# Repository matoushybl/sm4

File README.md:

# SM4 Stepper motor controller

This repository contains everything related to the SM4 Stepper motor controller project.

The project structure is as follows:
```
.github/ ... workflows for CI, releases, etc.
Hardware/ ... everything related to hardware - KiCAD projects, DS, etc.
Poster/ ... source file for a future poster
Software/ ... the controller and embedded firmware
Thesis/ ... the TeX source code for my Master's Thesis
```

## Authors
* Matous Hybl

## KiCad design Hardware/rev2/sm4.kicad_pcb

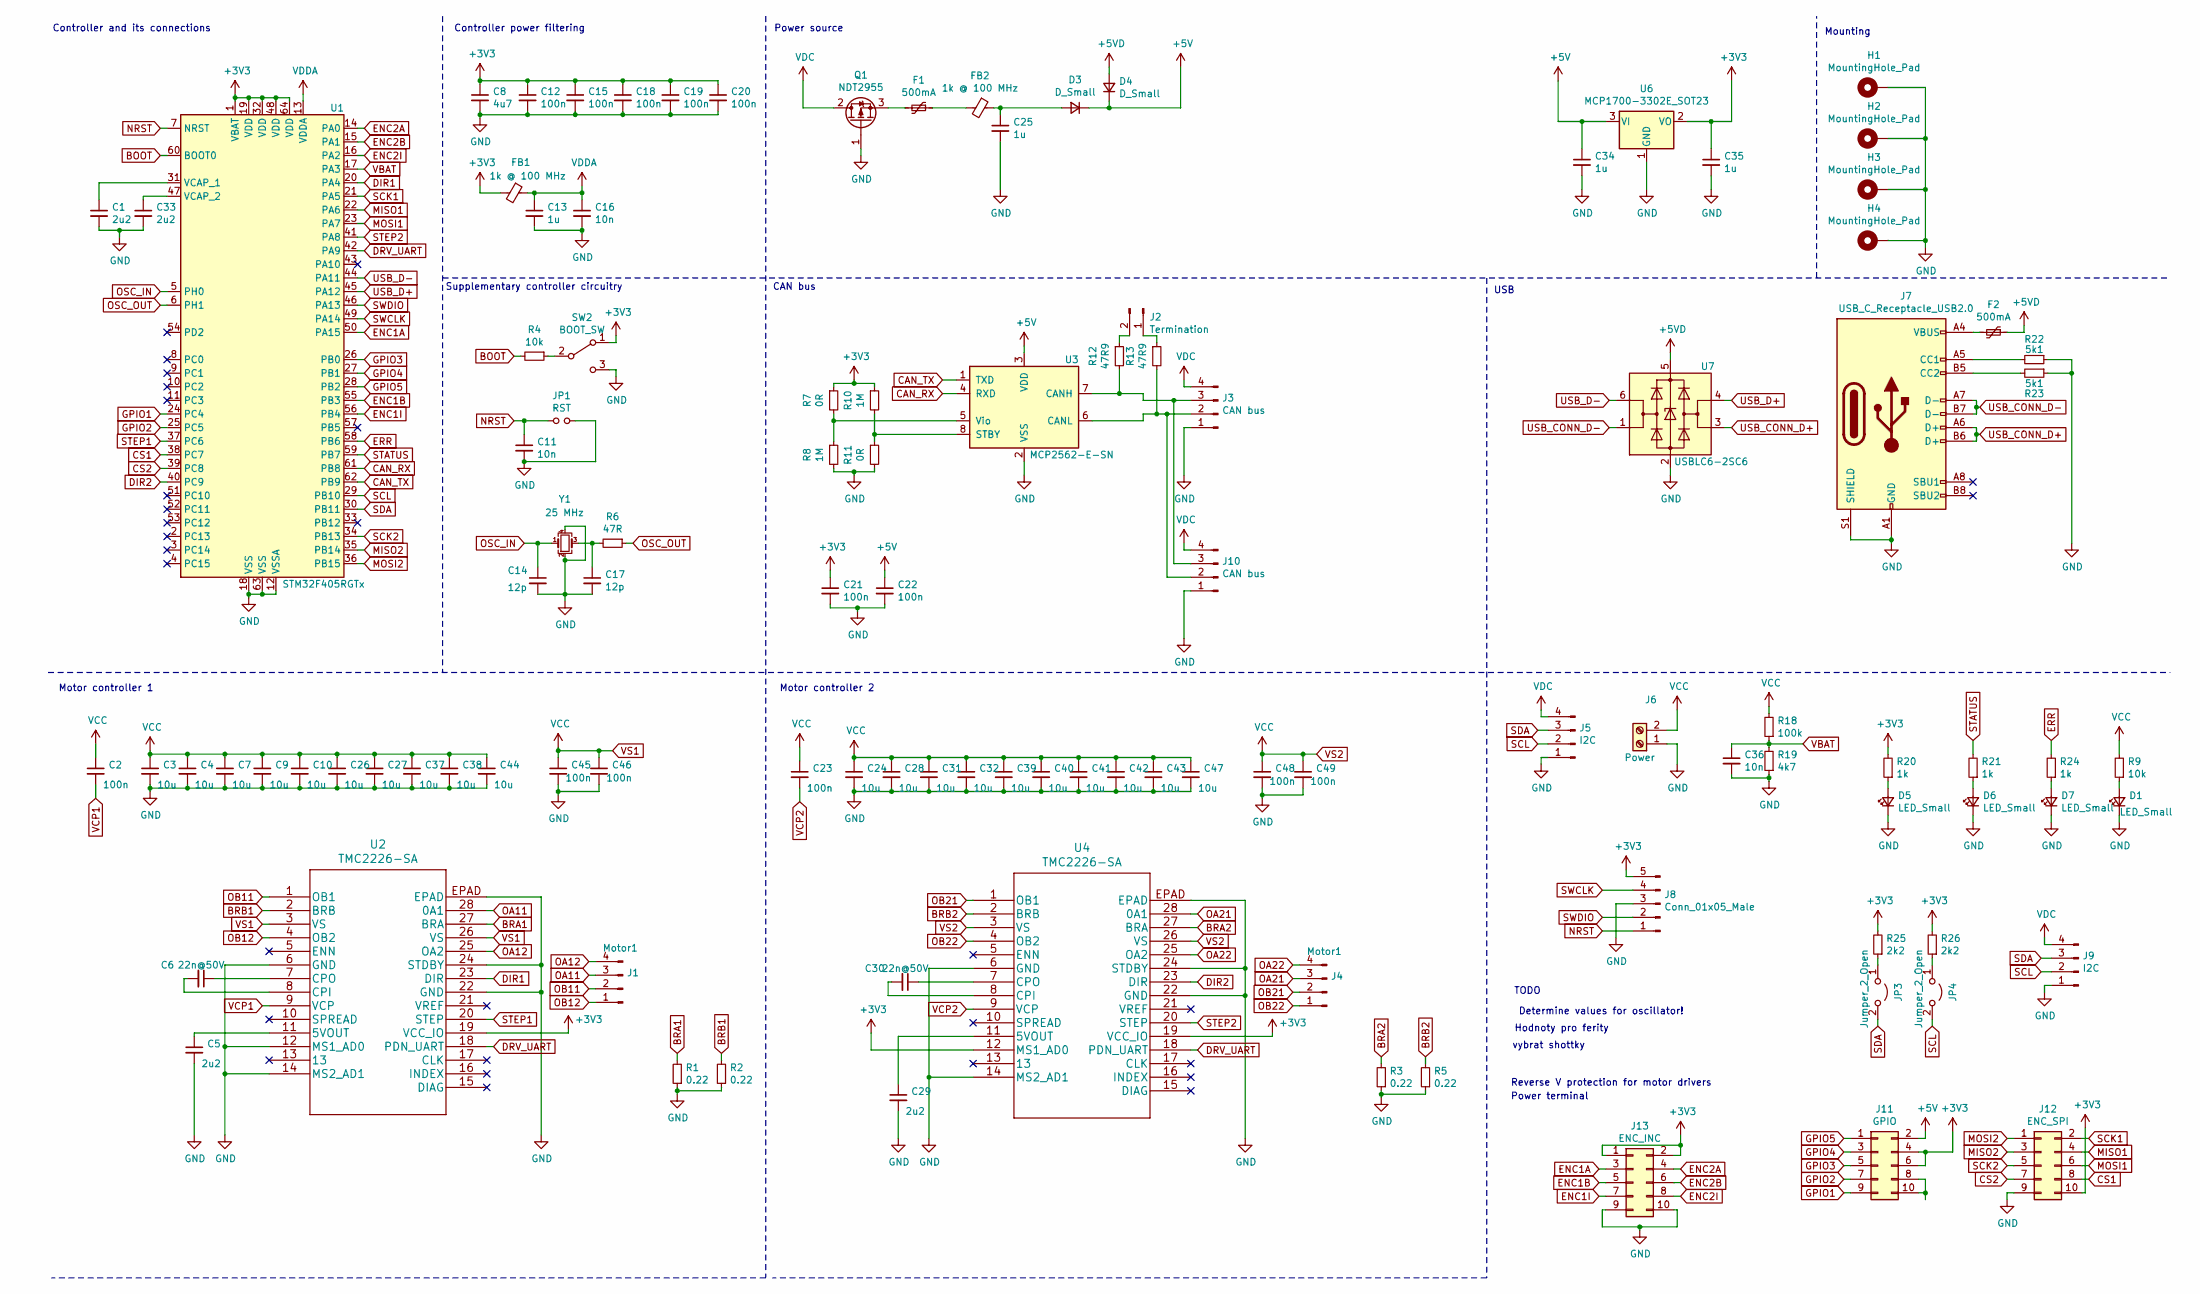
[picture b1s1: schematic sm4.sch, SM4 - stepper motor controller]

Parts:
C1, C33: 2u2; C_0603_1608Metric_Pad1.08x0.95mm_HandSolder; LCSC C23630
C2, C23, C45, C46, C48, C49: 100n; C_0603_1608Metric_Pad1.08x0.95mm_HandSolder; LCSC C14663
C3, C4, C7, C9, C10, C24, C26, C27, C28, C31, C32, C37, C38, C39, C40, C41, C42, C43, C44, C47: 10u; C_1206_3216Metric_Pad1.33x1.80mm_HandSolder; LCSC C13585
C5, C29: 2u2; C_0603_1608Metric_Pad1.08x0.95mm_HandSolder; LCSC C13585
C6, C30: 22n@50V; C_0402_1005Metric_Pad0.74x0.62mm_HandSolder; LCSC C1532
C8: 4u7; C_0603_1608Metric_Pad1.08x0.95mm_HandSolder; LCSC C19666
C11: 10n; C_0603_1608Metric_Pad1.08x0.95mm_HandSolder; LCSC C57112
C12, C15, C18, C19, C20, C21, C22: 100n; C_0402_1005Metric_Pad0.74x0.62mm_HandSolder; LCSC C1525
C13, C34, C35: 1u; C_0603_1608Metric_Pad1.08x0.95mm_HandSolder; LCSC C15849
C14, C17: 12p; C_0402_1005Metric_Pad0.74x0.62mm_HandSolder; LCSC C1547
C16, C36: 10n; C_0402_1005Metric_Pad0.74x0.62mm_HandSolder; LCSC C15195
C25: 1u; C_1206_3216Metric_Pad1.33x1.80mm_HandSolder; LCSC C1848
D1, D5: LED_Small; LED_0603_1608Metric_Pad1.05x0.95mm_HandSolder; LCSC C72038
D3, D4: D_Small; D_SOD-123; LCSC C8598
D6: LED_Small; LED_0603_1608Metric_Pad1.05x0.95mm_HandSolder; LCSC C72043
D7: LED_Small; LED_0603_1608Metric_Pad1.05x0.95mm_HandSolder; LCSC C2286
F1, F2: 500mA; Fuse_1206_3216Metric_Pad1.42x1.75mm_HandSolder; LCSC C70076
FB1, FB2: 1k @ 100 MHz; R_0603_1608Metric_Pad0.98x0.95mm_HandSolder
H1, H2, H3, H4: MountingHole_Pad; MountingHole_3.2mm_M3_Pad
J1, J4: Motor1; PinHeader_1x04_P2.54mm_Horizontal
J2: Termination; PinHeader_1x02_P2.54mm_Vertical
J3: CAN bus; Molex_SPOX_5268-04A_1x04_P2.50mm_Horizontal
J5: I2C; Molex_SPOX_5268-04A_1x04_P2.50mm_Horizontal
J6: Power; TerminalBlock_bornier-2_P5.08mm
J7: USB_C_Receptacle_USB2.0; USB_C_Receptacle_XKB_U262-16XN-4BVC11
J8: Conn_01x05_Male; Molex_SPOX_5267-05A_1x05_P2.50mm_Vertical
J9: I2C; Molex_SPOX_5267-04A_1x04_P2.50mm_Vertical
J10: CAN bus; Molex_SPOX_5267-04A_1x04_P2.50mm_Vertical
J11: GPIO; PinHeader_2x05_P1.27mm_Vertical
J12: ENC_SPI; PinHeader_2x05_P1.27mm_Vertical
J13: ENC_INC; PinHeader_2x05_P1.27mm_Vertical
JP1: RST; SolderJumper-2_P1.3mm_Open_RoundedPad1.0x1.5mm
JP3, JP4: Jumper_2_Open; SolderJumper-2_P1.3mm_Open_TrianglePad1.0x1.5mm
Q1: NDT2955; SOT-223-3_TabPin2; LCSC C194179
R1, R2, R3, R5: 0.22; R_1206_3216Metric_Pad1.30x1.75mm_HandSolder
R4: 10k; R_0402_1005Metric_Pad0.72x0.64mm_HandSolder; LCSC C25744
R6: 47R; R_0402_1005Metric_Pad0.72x0.64mm_HandSolder; LCSC C23182
R7, R11: 0R; R_0402_1005Metric_Pad0.72x0.64mm_HandSolder; LCSC C17168
R8, R10: 1M; R_0402_1005Metric_Pad0.72x0.64mm_HandSolder
R9: 10k; R_0402_1005Metric_Pad0.72x0.64mm_HandSolder; LCSC C25879
R12, R13: 47R9; R_0603_1608Metric_Pad0.98x0.95mm_HandSolder; LCSC C23182
R18: 100k; R_0402_1005Metric_Pad0.72x0.64mm_HandSolder; LCSC C25741
R19: 4k7; R_0402_1005Metric_Pad0.72x0.64mm_HandSolder; LCSC C25900
R20, R21, R24: 1k; R_0402_1005Metric_Pad0.72x0.64mm_HandSolder; LCSC C25879
R22, R23: 5k1; R_0402_1005Metric_Pad0.72x0.64mm_HandSolder; LCSC C25905
R25, R26: 2k2; R_0402_1005Metric_Pad0.72x0.64mm_HandSolder; LCSC C25879
SW2: BOOT_SW; SW_SPDT_PCM12
U1: STM32F405RGTx; LQFP-64_10x10mm_P0.5mm; LCSC C15742
U2, U4: TMC2226-SA
U3: MCP2562-E-SN; SOIC-8_3.9x4.9mm_P1.27mm; LCSC C53609
U6: MCP1700-3302E_SOT23; SOT-23; LCSC C39051
U7: USBLC6-2SC6; SOT-23-6; LCSC C7519
Y1: 25 MHz; Crystal_SMD_3225-4Pin_3.2x2.5mm_HandSoldering; LCSC C9006

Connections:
+3V3: C8.1, C12.1, C15.1, C18.1, C19.1, C20.1, C21.1, C35.1, FB1.2, J8.5, J11.4, J11.6, J12.10, J13.1, J13.2, R7.1, R10.1, R20.2, R25.2, R26.2, SW2.1 (A), U1.1 (VBAT), U1.19 (VDD), U1.32 (VDD), U1.48 (VDD), U1.64 (VDD), U2.19 (VCC_IO), U4.12 (MS1_AD0), U4.19 (VCC_IO), U6.2 (VO)
+5V: C22.1, C34.1, D3.1 (K), D4.1 (K), J11.2, U3.3 (VDD), U6.3 (VI)
+5VD: D4.2 (A), F2.1, U7.5 (VBUS)
BOOT: R4.2, U1.60 (BOOT0)
BRA1: R1.2, U2.27 (BRA)
BRA2: R3.2, U4.27 (BRA)
BRB1: R2.2, U2.2 (BRB)
BRB2: R5.2, U4.2 (BRB)
CAN_RX: U1.61 (PB8), U3.4 (RXD)
CAN_TX: U1.62 (PB9), U3.1 (TXD)
CS1: J12.8, U1.38 (PC7)
CS2: J12.7, U1.39 (PC8)
DIR1: U1.20 (PA4), U2.23 (DIR)
DIR2: U1.40 (PC9), U4.23 (DIR)
DRV_UART: U1.42 (PA9), U2.18 (PDN_UART), U4.18 (PDN_UART)
ENC1A: J13.3, U1.50 (PA15)
ENC1B: J13.5, U1.55 (PB3)
ENC1I: J13.7, U1.56 (PB4)
ENC2A: J13.4, U1.14 (PA0)
ENC2B: J13.6, U1.15 (PA1)
ENC2I: J13.8, U1.16 (PA2)
ERR: R24.2, U1.58 (PB6)
GND: C1.2, C3.2, C4.2, C5.2, C7.2, C8.2, C9.2, C10.2, C11.2, C12.2, C13.2, C14.2, C15.2, C16.2, C17.2, C18.2, C19.2, C20.2, C21.2, C22.2, C24.2, C25.2, C26.2, C27.2, C28.2, C29.2, C31.2, C32.2, C33.2, C34.2, C35.2, C36.2, C37.2, C38.2, C39.2, C40.2, C41.2, C42.2, C43.2, C44.2, C45.2, C46.2, C47.2, C48.2, C49.2, D1.1 (K), D5.1 (K), D6.1 (K), D7.1 (K), H1.1, H2.1, H3.1, H4.1, J3.1, J5.1, J6.1, J7.A1 (GND), J7.A12 (GND), J7.B1 (GND), J7.B12 (GND), J7.S1 (SHIELD), J8.3, J9.1, J10.1, J12.9, J13.9, J13.10, JP1.2, Q1.1 (G), R1.1, R2.1, R3.1, R5.1, R8.2, R11.2, R19.1, R22.1, R23.1, SW2.3 (C), U1.12 (VSSA), U1.18 (VSS), U1.63 (VSS), U2.6 (GND), U2.12 (MS1_AD0), U2.14 (MS2_AD1), U2.22 (GND), U2.24 (STDBY), U2.EPAD, U3.2 (VSS), U4.6 (GND), U4.14 (MS2_AD1), U4.22 (GND), U4.24 (STDBY), U4.EPAD, U6.1 (GND)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
GPIO1: J11.9, U1.24 (PC4)
GPIO2: J11.7, U1.25 (PC5)
GPIO3: J11.5, U1.26 (PB0)
GPIO4: J11.3, U1.27 (PB1)
GPIO5: J11.1, U1.28 (PB2)
MISO1: J12.4, U1.22 (PA6)
MISO2: J12.3, U1.35 (PB14)
MOSI1: J12.6, U1.23 (PA7)
MOSI2: J12.1, U1.36 (PB15)
NRST: C11.1, J8.1, JP1.1, U1.7 (NRST)
unnamed: C1.1, U1.31 (VCAP_1)
unnamed: C5.1, U2.11 (5VOUT)
unnamed: C6.1, U2.7 (CPO)
unnamed: C6.2, U2.8 (CPI)
unnamed: C17.1, R6.2, Y1.3
unnamed: C25.1, D3.2 (A), FB2.1
unnamed: C29.1, U4.11 (5VOUT)
unnamed: C30.1, U4.7 (CPO)
unnamed: C30.2, U4.8 (CPI)
unnamed: C33.1, U1.47 (VCAP_2)
unnamed: D1.2 (A), R9.1
unnamed: D5.2 (A), R20.1
unnamed: D6.2 (A), R21.1
unnamed: D7.2 (A), R24.1
unnamed: F1.1, FB2.2
unnamed: F1.2, Q1.3 (S)
unnamed: F2.2, J7.A4 (VBUS), J7.A9 (VBUS), J7.B4 (VBUS), J7.B9 (VBUS)
unnamed: J2.1, R13.1
unnamed: J2.2, R12.1
unnamed: J7.A5 (CC1), R22.2
unnamed: J7.B5 (CC2), R23.2
unnamed: J3.2, J10.2, R13.2, U3.6 (CANL)
unnamed: J3.3, J10.3, R12.2, U3.7 (CANH)
unnamed: J11.8, J11.10
unnamed: JP3.1 (A), R25.1
unnamed: JP4.1 (A), R26.1
unnamed: R4.1, SW2.2 (B)
unnamed: R7.2, R8.1, U3.5 (Vio)
unnamed: R10.2, R11.1, U3.8 (STBY)
OA11: J1.3, U2.28 (0A1)
OA12: J1.4, U2.25 (OA2)
OA21: J4.3, U4.28 (0A1)
OA22: J4.4, U4.25 (OA2)
OB11: J1.2, U2.1 (OB1)
OB12: J1.1, U2.4 (OB2)
OB21: J4.2, U4.1 (OB1)
OB22: J4.1, U4.4 (OB2)
OSC_IN: C14.1, U1.5 (PH0), Y1.1
OSC_OUT: R6.1, U1.6 (PH1)
SCK1: J12.2, U1.21 (PA5)
SCK2: J12.5, U1.34 (PB13)
SCL: J5.2, J9.2, JP4.2 (B), U1.29 (PB10)
SDA: J5.3, J9.3, JP3.2 (B), U1.30 (PB11)
STATUS: R21.2, U1.59 (PB7)
STEP1: U1.37 (PC6), U2.20 (STEP)
STEP2: U1.41 (PA8), U4.20 (STEP)
SWCLK: J8.4, U1.49 (PA14)
SWDIO: J8.2, U1.46 (PA13)
USB_CONN_D+: J7.A6 (D+), J7.B6 (D+), U7.3 (I/O2)
USB_CONN_D-: J7.A7 (D-), J7.B7 (D-), U7.1 (I/O1)
USB_D+: U1.45 (PA12), U7.4 (I/O2)
USB_D-: U1.44 (PA11), U7.6 (I/O1)
VBAT: C36.1, R18.1, R19.2, U1.17 (PA3)
VCP1: C2.2, U2.9 (VCP)
VCP2: C23.2, U4.9 (VCP)
VDC: J3.4, J5.4, J9.4, J10.4, Q1.2 (D)
VDDA: C13.1, C16.1, FB1.1, U1.13 (VDDA)
VS1: C2.1, C3.1, C4.1, C7.1, C9.1, C10.1, C23.1, C24.1, C26.1, C27.1, C28.1, C31.1, C32.1, C37.1, C38.1, C39.1, C40.1, C41.1, C42.1, C43.1, C44.1, C45.1, C46.1, C47.1, C48.1, C49.1, J6.2, R9.2, R18.2, U2.3 (VS), U2.26 (VS), U4.3 (VS), U4.26 (VS)

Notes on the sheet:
Determine values for oscillator!
Controller and its connections
Controller power filtering
Supplementary controller circuitry
Power source
Mounting
TODO
Hodnoty pro ferity
vybrat shottky
Motor controller 1
Motor controller 2
Reverse V protection for motor drivers
CAN bus
USB
Power terminal

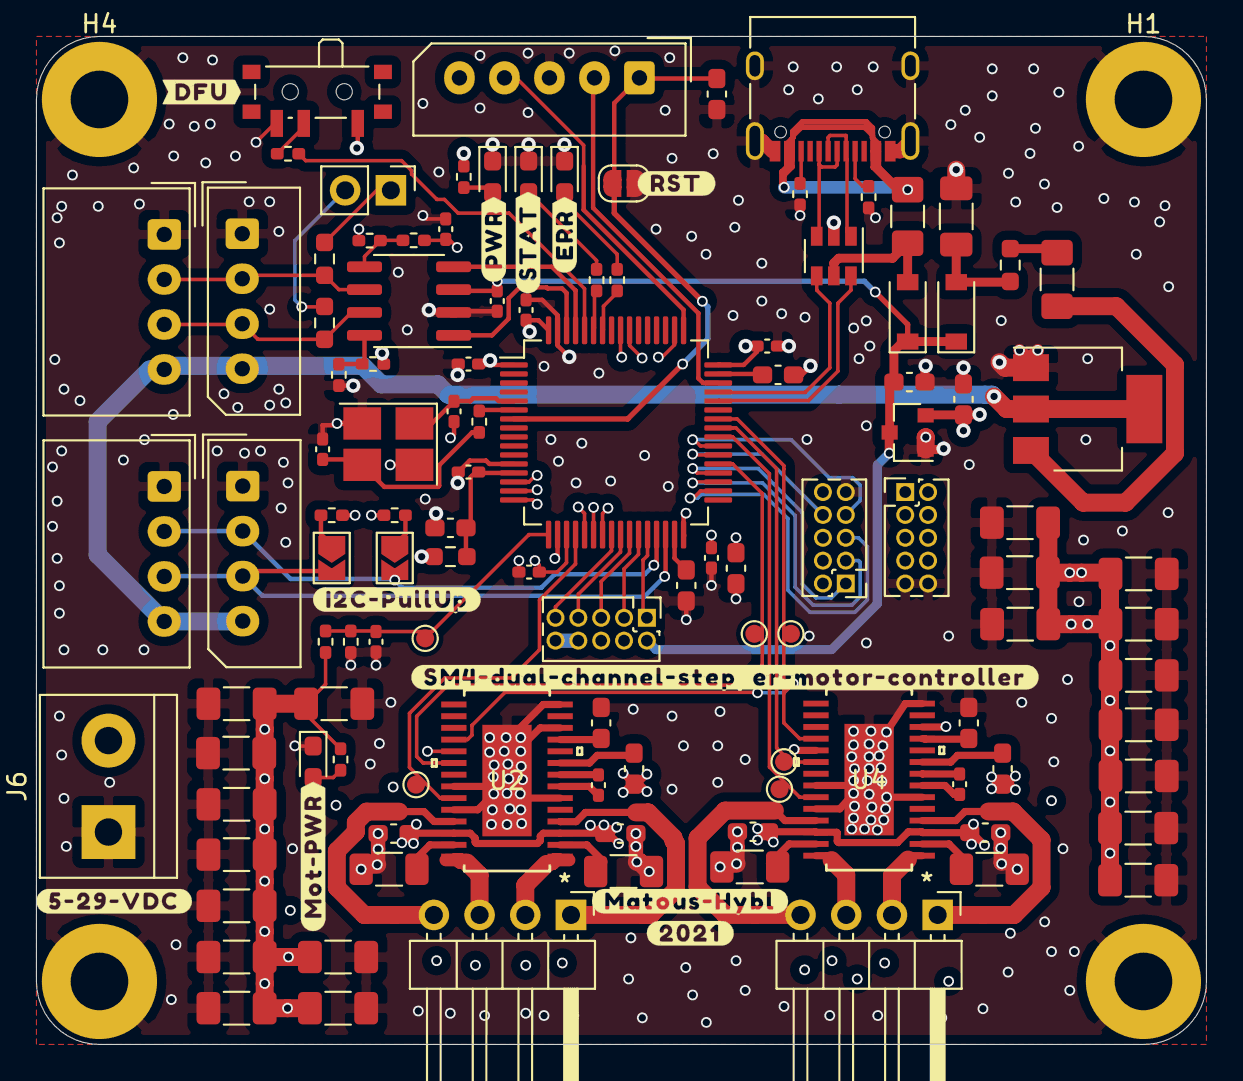
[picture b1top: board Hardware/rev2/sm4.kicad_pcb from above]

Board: 4 copper layers, 65.0 x 56.0 mm, 110 parts (0 on the bottom side), 91 nets.

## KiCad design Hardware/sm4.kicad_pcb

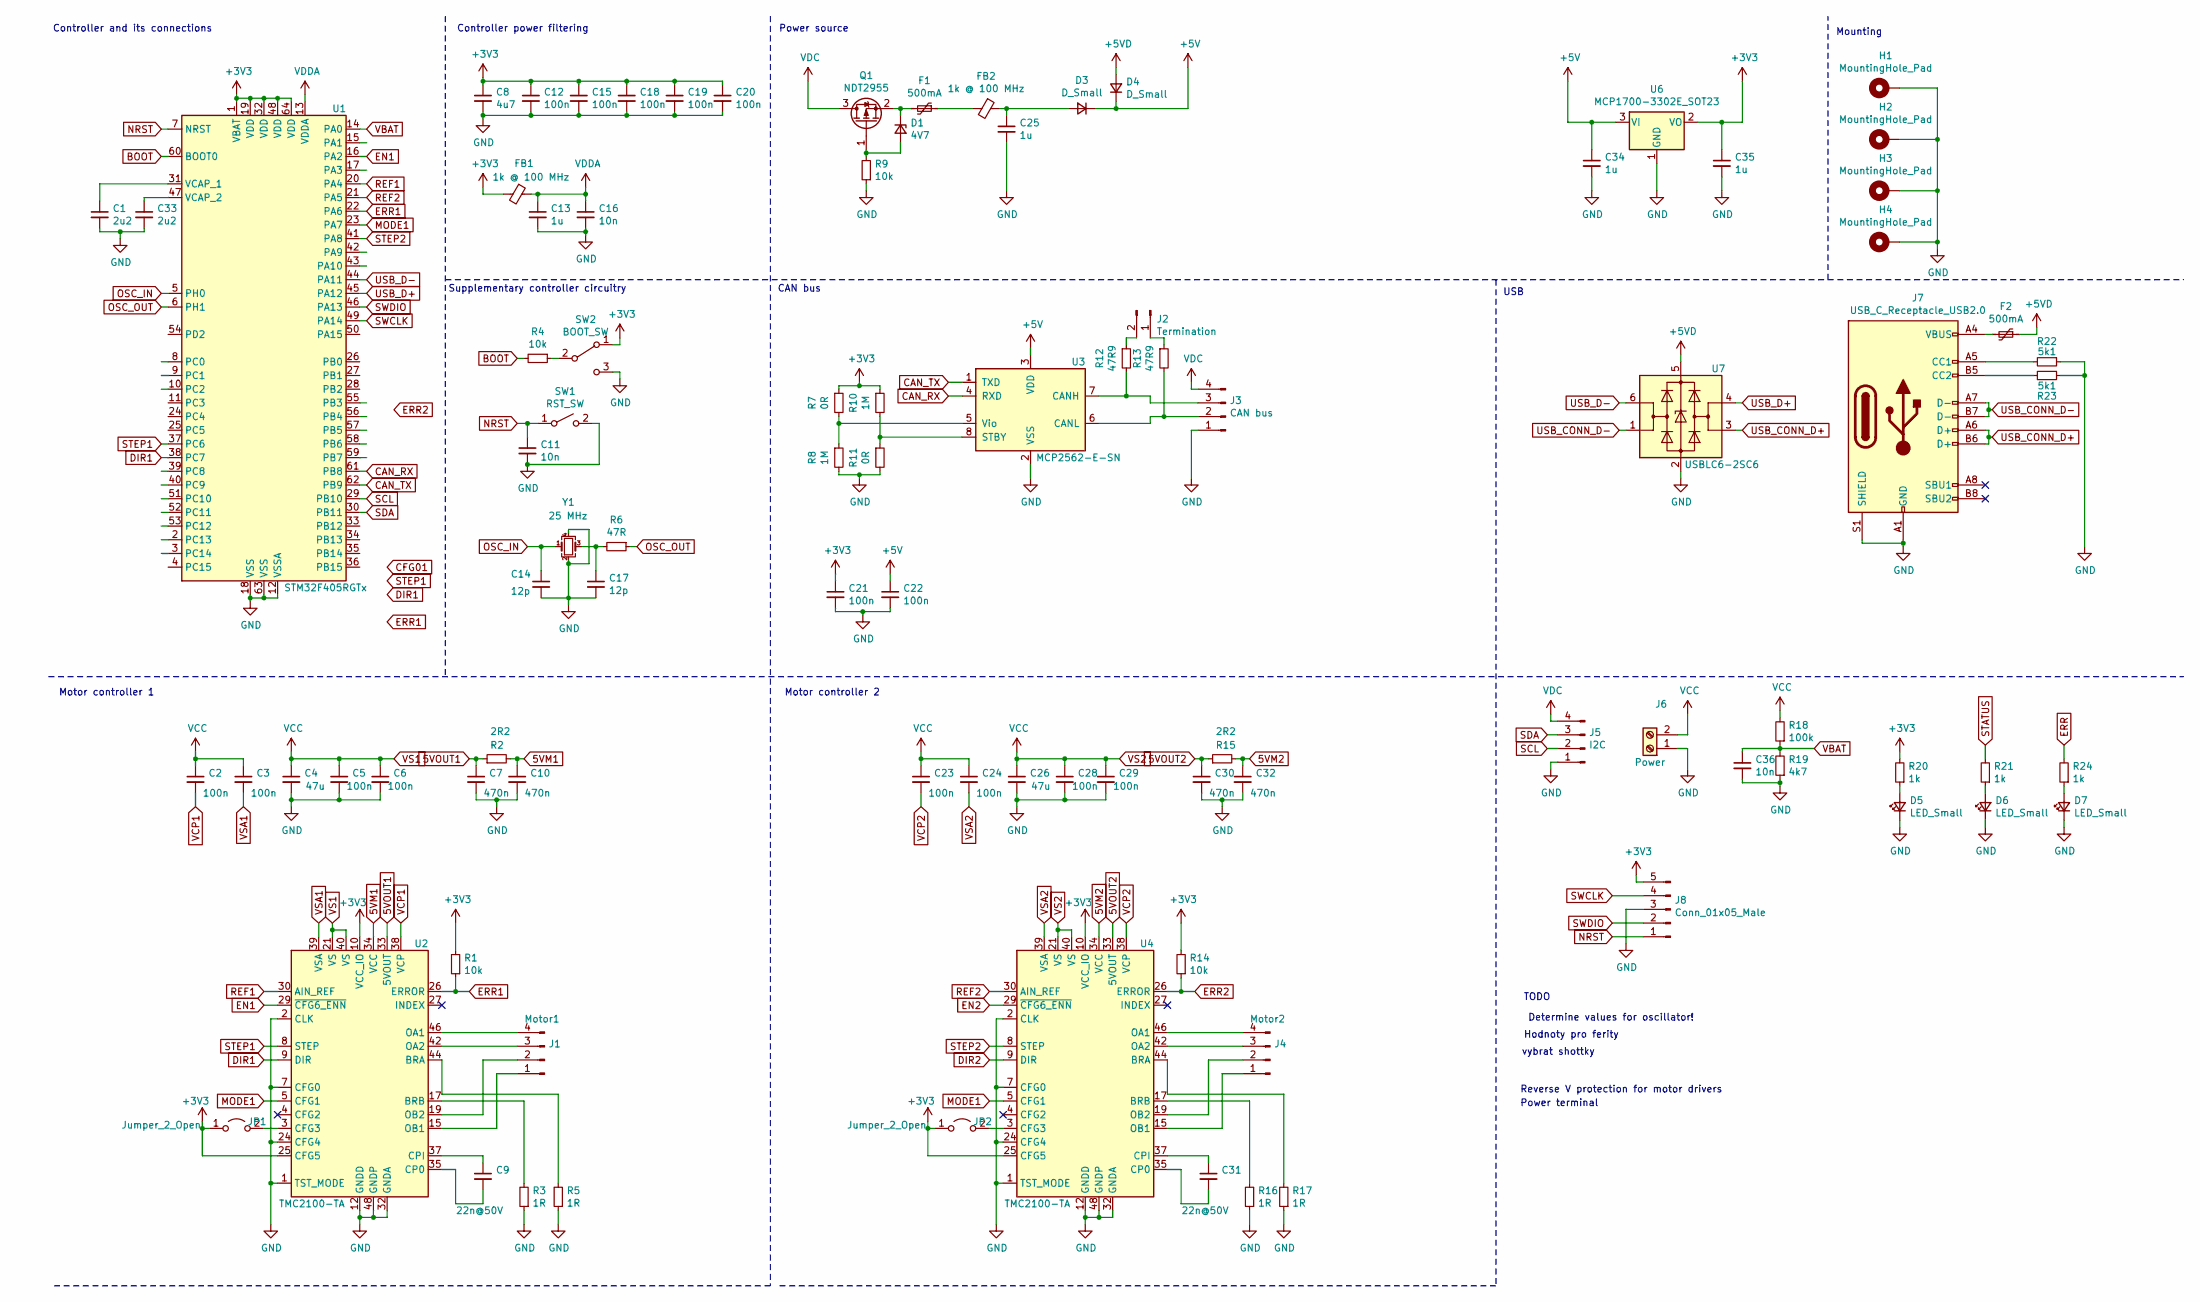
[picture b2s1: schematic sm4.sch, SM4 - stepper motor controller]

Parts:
C1, C33: 2u2; C_0603_1608Metric_Pad1.08x0.95mm_HandSolder
C2, C3, C5, C6, C23, C24, C28, C29: 100n; C_0805_2012Metric_Pad1.18x1.45mm_HandSolder
C4, C26: 47u; C_Elec_8x6.2
C7, C10, C30, C32: 470n; C_0603_1608Metric_Pad1.08x0.95mm_HandSolder
C8: 4u7; C_0603_1608Metric_Pad1.08x0.95mm_HandSolder
C9, C31: 22n@50V; C_0603_1608Metric_Pad1.08x0.95mm_HandSolder
C11: 10n; C_0603_1608Metric_Pad1.08x0.95mm_HandSolder
C12, C15, C18, C19, C20, C21, C22: 100n; C_0402_1005Metric_Pad0.74x0.62mm_HandSolder
C13, C34, C35: 1u; C_0603_1608Metric_Pad1.08x0.95mm_HandSolder
C14, C17: 12p; C_0402_1005Metric_Pad0.74x0.62mm_HandSolder
C16, C36: 10n; C_0402_1005Metric_Pad0.74x0.62mm_HandSolder
C25: 1u; C_1206_3216Metric_Pad1.33x1.80mm_HandSolder
D1: 4V7; D_SOD-123
D3, D4: D_Small; D_SOD-123
D5, D6, D7: LED_Small; LED_0603_1608Metric_Pad1.05x0.95mm_HandSolder
F1, F2: 500mA; Fuse_1206_3216Metric_Pad1.42x1.75mm_HandSolder
FB1, FB2: 1k @ 100 MHz; R_0603_1608Metric_Pad0.98x0.95mm_HandSolder
H1, H2, H3, H4: MountingHole_Pad; MountingHole_3.2mm_M3_Pad
J1: Motor1; PinHeader_1x04_P2.54mm_Horizontal
J2: Termination; PinHeader_1x02_P2.54mm_Vertical
J3: CAN bus; Molex_SPOX_5268-04A_1x04_P2.50mm_Horizontal
J4: Motor2; PinHeader_1x04_P2.54mm_Horizontal
J5: I2C; Molex_SPOX_5268-04A_1x04_P2.50mm_Horizontal
J6: Power; TerminalBlock_bornier-2_P5.08mm
J7: USB_C_Receptacle_USB2.0; USB_C_Receptacle_GCT_USB4085
J8: Conn_01x05_Male; Molex_SPOX_5267-05A_1x05_P2.50mm_Vertical
JP1, JP2: Jumper_2_Open; SolderJumper-2_P1.3mm_Open_TrianglePad1.0x1.5mm
Q1: NDT2955; SOT-23
R1, R4: 10k; R_0402_1005Metric_Pad0.72x0.64mm_HandSolder
R2, R15: 2R2; R_0603_1608Metric_Pad0.98x0.95mm_HandSolder
R3, R5, R16, R17: 1R; R_0603_1608Metric_Pad0.98x0.95mm_HandSolder
R6: 47R; R_0402_1005Metric_Pad0.72x0.64mm_HandSolder
R7, R11: 0R; R_0402_1005Metric_Pad0.72x0.64mm_HandSolder
R8, R10: 1M; R_0402_1005Metric_Pad0.72x0.64mm_HandSolder
R9, R14: 10k; R_0603_1608Metric_Pad0.98x0.95mm_HandSolder
R12, R13: 47R9; R_0603_1608Metric_Pad0.98x0.95mm_HandSolder
R18: 100k; R_0402_1005Metric_Pad0.72x0.64mm_HandSolder
R19: 4k7; R_0402_1005Metric_Pad0.72x0.64mm_HandSolder
R20, R21, R24: 1k; R_0402_1005Metric_Pad0.72x0.64mm_HandSolder
R22, R23: 5k1; R_0402_1005Metric_Pad0.72x0.64mm_HandSolder
SW1: RST_SW; PinHeader_1x02_P2.54mm_Vertical
SW2: BOOT_SW; SW_SPDT_PCM12
U1: STM32F405RGTx; LQFP-64_10x10mm_P0.5mm
U2, U4: TMC2100-TA; TQFP-48-1EP_7x7mm_P0.5mm_EP5x5mm_ThermalVias
U3: MCP2562-E-SN; SOIC-8_3.9x4.9mm_P1.27mm
U6: MCP1700-3302E_SOT23; SOT-23
U7: USBLC6-2SC6; SOT-23-6
Y1: 25 MHz; Crystal_SMD_3225-4Pin_3.2x2.5mm_HandSoldering

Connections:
5VM1: C10.1, R2.2, U2.34 (VCC)
5VM2: C32.1, R15.2, U4.34 (VCC)
5VOUT1: C7.1, R2.1, U2.33 (5VOUT)
5VOUT2: C30.1, R15.1, U4.33 (5VOUT)
+3V3: C8.1, C12.1, C15.1, C18.1, C19.1, C20.1, C21.1, C35.1, FB1.2, J8.5, JP1.1 (A), JP2.1 (A), R1.2, R7.1, R10.1, R14.2, R20.2, SW2.1 (A), U1.1 (VBAT), U1.19 (VDD), U1.32 (VDD), U1.48 (VDD), U1.64 (VDD), U2.10 (VCC_IO), U2.25 (CFG5), U4.10 (VCC_IO), U4.25 (CFG5), U6.2 (VO)
+5V: C22.1, C34.1, D3.1 (K), D4.1 (K), U3.3 (VDD), U6.3 (VI)
+5VD: D4.2 (A), F2.1, U7.5 (VBUS)
BOOT: R4.2, U1.60 (BOOT0)
CAN_RX: U1.61 (PB8), U3.4 (RXD)
CAN_TX: U1.62 (PB9), U3.1 (TXD)
DIR1: U1.38 (PC7), U2.9 (DIR)
EN1: U1.16 (PA2), U2.29 (~CFG6_ENN)
ERR1: R1.1, U1.22 (PA6), U2.26 (ERROR)
ERR2: R14.1, U4.26 (ERROR)
GND: C1.2, C4.2, C5.2, C6.2, C7.2, C8.2, C10.2, C11.2, C12.2, C13.2, C14.2, C15.2, C16.2, C17.2, C18.2, C19.2, C20.2, C21.2, C22.2, C25.2, C26.2, C28.2, C29.2, C30.2, C32.2, C33.2, C34.2, C35.2, C36.2, D5.1 (K), D6.1 (K), D7.1 (K), H1.1, H2.1, H3.1, H4.1, J3.1, J5.1, J6.1, J7.A1 (GND), J7.A12 (GND), J7.B1 (GND), J7.B12 (GND), J7.S1 (SHIELD), J8.3, R3.1, R5.1, R8.2, R9.1, R11.2, R16.1, R17.1, R19.1, R22.1, R23.1, SW1.2 (B), SW2.3 (C), U1.12 (VSSA), U1.18 (VSS), U1.63 (VSS), U2.1 (TST_MODE), U2.2 (CLK), U2.6 (GNDD), U2.7 (CFG0), U2.12 (GNDD), U2.13 (GNDP), U2.24 (CFG4), U2.31 (GNDD), U2.32 (GNDA), U2.36 (GNDD), U2.48 (GNDP), U2.49 (GNDD), U3.2 (VSS), U4.1 (TST_MODE), U4.2 (CLK), U4.6 (GNDD), U4.7 (CFG0), U4.12 (GNDD), U4.13 (GNDP), U4.24 (CFG4), U4.31 (GNDD), U4.32 (GNDA), U4.36 (GNDD), U4.48 (GNDP), U4.49 (GNDD), U6.1 (GND), U7.2 (GND), Y1.2, Y1.4
MODE1: U1.23 (PA7), U2.5 (CFG1), U4.5 (CFG1)
NRST: C11.1, J8.1, SW1.1 (A), U1.7 (NRST)
unnamed: C1.1, U1.31 (VCAP_1)
unnamed: C9.1, U2.37 (CPI)
unnamed: C9.2, U2.35 (CP0)
unnamed: C17.1, R6.2, Y1.3
unnamed: C25.1, D3.2 (A), FB2.1
unnamed: C31.1, U4.37 (CPI)
unnamed: C31.2, U4.35 (CP0)
unnamed: C33.1, U1.47 (VCAP_2)
unnamed: D1.1 (K), F1.2, Q1.2 (S)
unnamed: D1.2 (A), Q1.1 (G), R9.2
unnamed: D5.2 (A), R20.1
unnamed: D6.2 (A), R21.1
unnamed: D7.2 (A), R24.1
unnamed: F1.1, FB2.2
unnamed: F2.2, J7.A4 (VBUS), J7.A9 (VBUS), J7.B4 (VBUS), J7.B9 (VBUS)
unnamed: J1.1, U2.15 (OB1)
unnamed: J1.2, U2.19 (OB2)
unnamed: J1.3, U2.42 (OA2)
unnamed: J1.4, U2.46 (OA1)
unnamed: J2.1, R13.1
unnamed: J2.2, R12.1
unnamed: J3.2, R13.2, U3.6 (CANL)
unnamed: J3.3, R12.2, U3.7 (CANH)
unnamed: J4.1, U4.15 (OB1)
unnamed: J4.2, U4.19 (OB2)
unnamed: J4.3, U4.42 (OA2)
unnamed: J4.4, U4.46 (OA1)
unnamed: J7.A5 (CC1), R22.2
unnamed: J7.B5 (CC2), R23.2
unnamed: JP1.2 (B), U2.3 (CFG3)
unnamed: JP2.2 (B), U4.3 (CFG3)
unnamed: R3.2, U2.17 (BRB)
unnamed: R4.1, SW2.2 (B)
unnamed: R5.2, U2.44 (BRA)
unnamed: R7.2, R8.1, U3.5 (Vio)
unnamed: R10.2, R11.1, U3.8 (STBY)
unnamed: R16.2, U4.17 (BRB)
unnamed: R17.2, U4.44 (BRA)
OSC_IN: C14.1, U1.5 (PH0), Y1.1
OSC_OUT: R6.1, U1.6 (PH1)
REF1: U1.20 (PA4), U2.30 (AIN_REF)
REF2: U1.21 (PA5), U4.30 (AIN_REF)
SCL: J5.2, U1.29 (PB10)
SDA: J5.3, U1.30 (PB11)
STEP1: U1.37 (PC6), U2.8 (STEP)
STEP2: U1.41 (PA8), U4.8 (STEP)
SWCLK: J8.4, U1.49 (PA14)
SWDIO: J8.2, U1.46 (PA13)
USB_CONN_D+: J7.A6 (D+), J7.B6 (D+), U7.3 (I/O2)
USB_CONN_D-: J7.A7 (D-), J7.B7 (D-), U7.1 (I/O1)
USB_D+: U1.45 (PA12), U7.4 (I/O2)
USB_D-: U1.44 (PA11), U7.6 (I/O1)
VBAT: C36.1, R18.1, R19.2, U1.14 (PA0)
VCP1: C2.2, U2.38 (VCP)
VCP2: C23.2, U4.38 (VCP)
VDC: J3.4, J5.4, Q1.3 (D)
VDDA: C13.1, C16.1, FB1.1, U1.13 (VDDA)
VS1: C2.1, C3.1, C4.1, C5.1, C6.1, C23.1, C24.1, C26.1, C28.1, C29.1, J6.2, R18.2, U2.21 (VS), U2.40 (VS), U4.21 (VS), U4.40 (VS)
VSA1: C3.2, U2.39 (VSA)
VSA2: C24.2, U4.39 (VSA)

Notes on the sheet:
Determine values for oscillator!
Controller and its connections
Controller power filtering
Supplementary controller circuitry
Power source
Mounting
TODO
Hodnoty pro ferity
vybrat shottky
Motor controller 1
Motor controller 2
Reverse V protection for motor drivers
CAN bus
USB
Power terminal

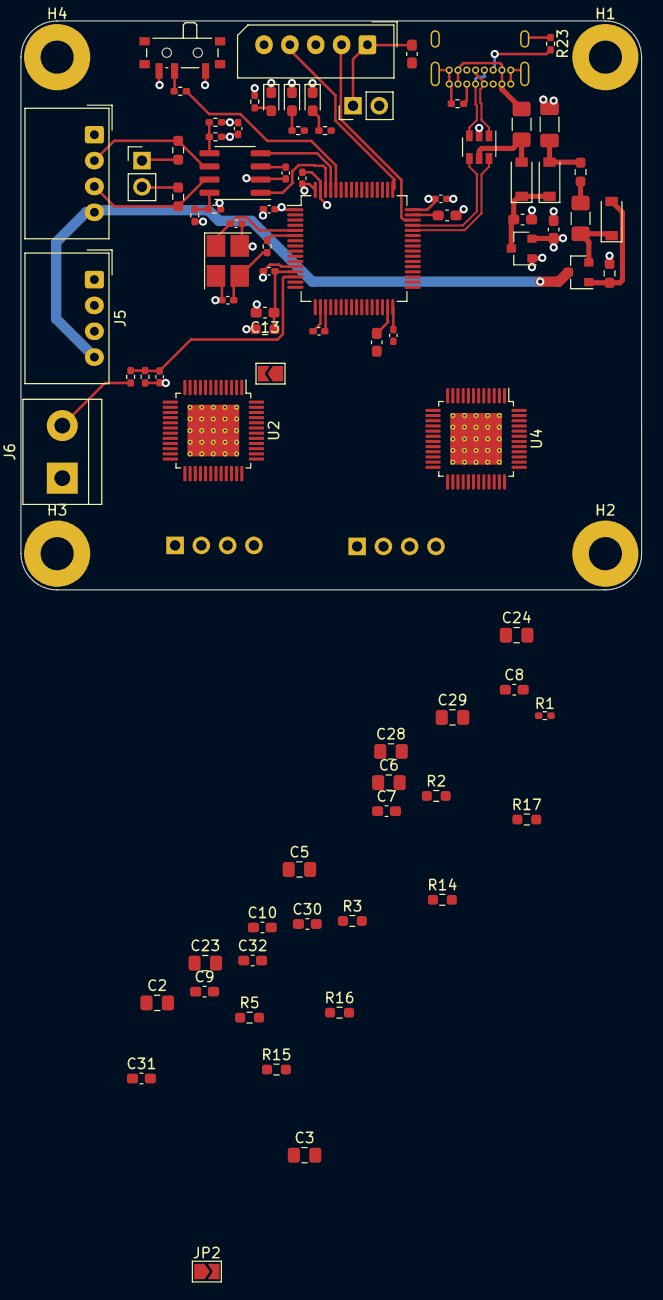
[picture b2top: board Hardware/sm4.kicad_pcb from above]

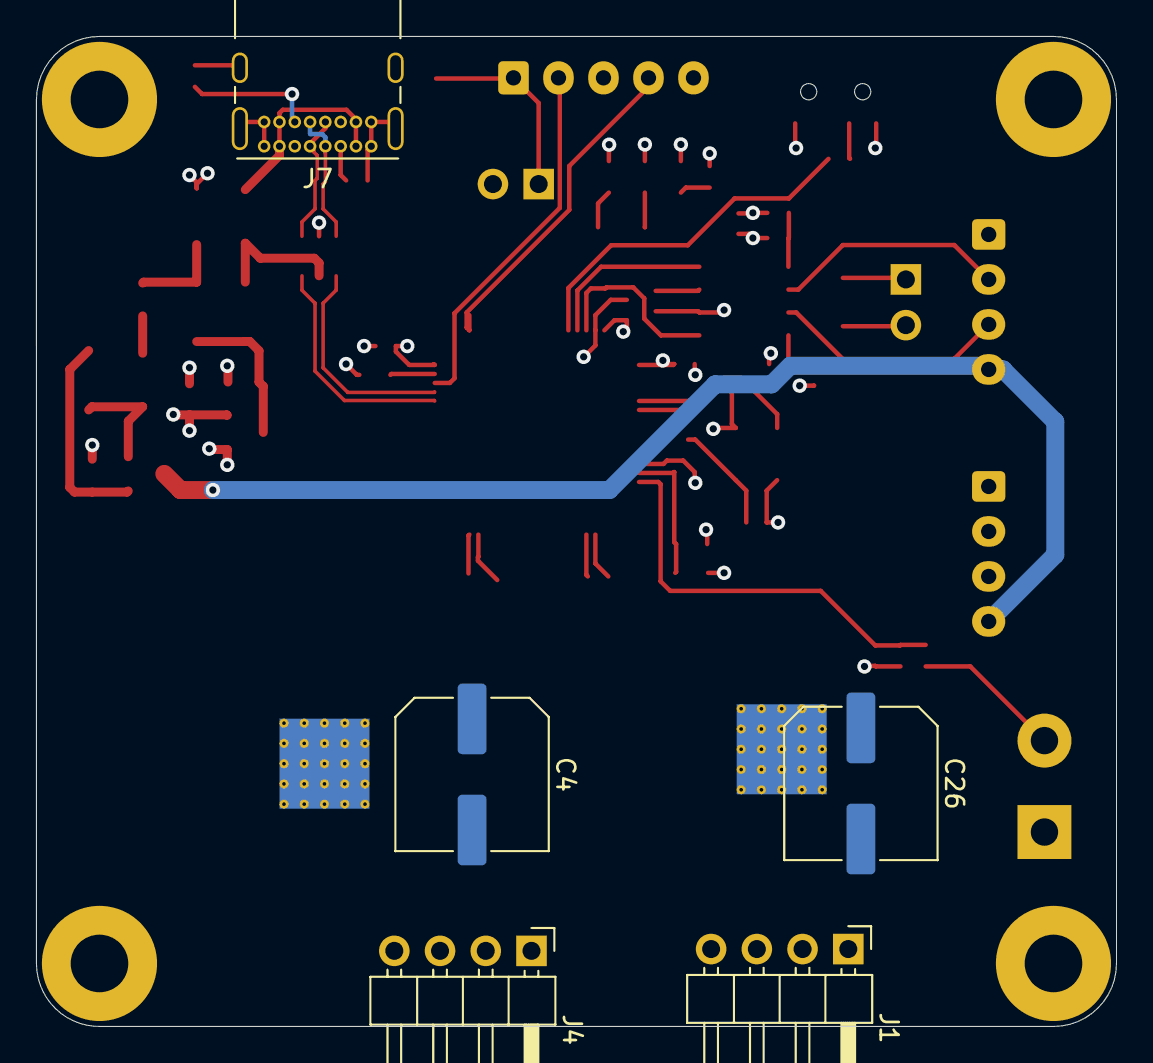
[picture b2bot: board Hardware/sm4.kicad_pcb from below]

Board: 4 copper layers, 60.0 x 55.0 mm, 93 parts (5 on the bottom side), 77 nets.

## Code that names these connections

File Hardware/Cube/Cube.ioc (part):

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Mcu.Name=STM32F405RGTx
Mcu.Package=LQFP64
Mcu.UserName=STM32F405RGTx
PA0-WKUP.GPIOParameters=GPIO_Label
PA0-WKUP.GPIO_Label=ENC2A
PA0-WKUP.Signal=S_TIM5_CH1
PA1.GPIOParameters=GPIO_Label
PA1.GPIO_Label=ENC2B
PA1.Signal=S_TIM5_CH2
PA11.Mode=Host_Only
PA11.Signal=USB_OTG_FS_DM
PA12.Mode=Host_Only
PA12.Signal=USB_OTG_FS_DP
PA13.Mode=Serial_Wire
PA13.Signal=SYS_JTMS-SWDIO
PA14.Mode=Serial_Wire
PA14.Signal=SYS_JTCK-SWCLK
PA15.GPIOParameters=GPIO_Label
PA15.GPIO_Label=ENC1A
PA15.Signal=S_TIM2_CH1_ETR
PA2.GPIOParameters=GPIO_Label
PA2.GPIO_Label=ENC2I
PA2.Signal=GPXTI2
PA3.GPIOParameters=GPIO_Label
PA3.GPIO_Label=VBAT
PA3.Signal=GPIO_Output
PA4.GPIOParameters=GPIO_Label
PA4.GPIO_Label=DIR1
PA4.Signal=GPIO_Output
PA5.Mode=Full_Duplex_Master
PA5.Signal=SPI1_SCK
PA6.Mode=Full_Duplex_Master
PA6.Signal=SPI1_MISO
PA7.Mode=Full_Duplex_Master
PA7.Signal=SPI1_MOSI
PA8.GPIOParameters=GPIO_Label
PA8.GPIO_Label=STEP2
PA8.Signal=S_TIM1_CH1
PA9.GPIOParameters=GPIO_Label
PA9.GPIO_Label=DRV_UART
PA9.Mode=Half_duplex(single_wire_mode)
PA9.Signal=USART1_TX
PB0.GPIOParameters=GPIO_Label
PB0.GPIO_Label=GPIO3
PB0.Signal=GPIO_Output
PB1.GPIOParameters=GPIO_Label
PB1.GPIO_Label=GPIO4
PB1.Signal=GPIO_Output
PB10.Mode=I2C
PB10.Signal=I2C2_SCL
PB11.Mode=I2C
PB11.Signal=I2C2_SDA
PB13.Mode=Full_Duplex_Master
PB13.Signal=SPI2_SCK
PB14.Mode=Full_Duplex_Master
PB14.Signal=SPI2_MISO
PB15.Mode=Full_Duplex_Master
PB15.Signal=SPI2_MOSI
PB2.GPIOParameters=GPIO_Label
PB2.GPIO_Label=GPIO5
PB2.Signal=GPIO_Output
PB3.GPIOParameters=GPIO_Label
PB3.GPIO_Label=ENC1B
PB3.Signal=S_TIM2_CH2
PB4.GPIOParameters=GPIO_Label
PB4.GPIO_Label=ENC1I
PB4.Signal=GPXTI4
PB6.GPIOParameters=GPIO_Label
PB6.GPIO_Label=ERR_LED
PB6.Signal=GPIO_Output
PB7.GPIOParameters=GPIO_Label
PB7.GPIO_Label=STATUS_LED
PB7.Signal=GPIO_Output
PB8.Mode=Master
PB8.Signal=CAN1_RX
PB9.Mode=Master
PB9.Signal=CAN1_TX
PC4.GPIOParameters=GPIO_Label
PC4.GPIO_Label=GPIO1
PC4.Signal=GPIO_Output
PC5.GPIOParameters=GPIO_Label
PC5.GPIO_Label=GPIO2
PC5.Signal=GPIO_Output
PC6.GPIOParameters=GPIO_Label
PC6.GPIO_Label=STEP1
PC6.Signal=S_TIM8_CH1
PC7.GPIOParameters=GPIO_Label
PC7.GPIO_Label=CS1
PC7.Signal=GPIO_Output
PC8.GPIOParameters=GPIO_Label
PC8.GPIO_Label=CS2
PC8.Signal=GPIO_Output
PC9.GPIOParameters=GPIO_Label
PC9.GPIO_Label=DIR2
PC9.Signal=GPIO_Output
PH0-OSC_IN.Mode=HSE-External-Oscillator
PH0-OSC_IN.Signal=RCC_OSC_IN
PH1-OSC_OUT.Mode=HSE-External-Oscillator
PH1-OSC_OUT.Signal=RCC_OSC_OUT
RCC.HSE_VALUE=25000000
RCC.SYSCLKFreq_VALUE=168000000
RCC.SYSCLKSource=RCC_SYSCLKSOURCE_PLLCLK
board=custom

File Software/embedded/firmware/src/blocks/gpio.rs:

use crate::board::definitions::*;

pub struct GPIO {
    pub dir1: Dir1,
    pub dir2: Dir2,
    pub mode1: Mode1,
    pub mode2: Mode2,
    pub ref1: CurrentRef1Pin,
    pub ref2: CurrentRef2Pin,
    pub en1: En1,
    pub en2: En2,
    pub step1: Step1,
    pub step2: Step2,
    pub err1: Err1,
    pub err2: Err2,
    pub battery_voltage: BatteryVoltage,
    pub error_led: ErrorLED,
    pub status_led: StatusLED,
    pub can_rx: CANRx,
    pub can_tx: CANTx,
    pub scl: SCL,
    pub sda: SDA,
    pub usb_minus: USBDMinus,
    pub usb_plus: USBDPlus,
}

impl GPIO {
    pub fn configure(
        gpioa: stm32f4xx_hal::gpio::gpioa::Parts,
        gpiob: stm32f4xx_hal::gpio::gpiob::Parts,
        gpioc: stm32f4xx_hal::gpio::gpioc::Parts,
    ) -> Self {
        Self {
            dir1: gpioa.pa1.into_push_pull_output(),
            dir2: gpiob.pb12.into_push_pull_output(),
            mode1: gpioa.pa3.into_floating_input(),
            mode2: gpioa.pa9.into_floating_input(),
            ref1: gpioa.pa4.into_analog(),
            ref2: gpioa.pa5.into_analog(),
            en1: gpioa.pa6.into_floating_input(),
            en2: gpioa.pa7.into_floating_input(),
            step1: gpioc.pc6.into_alternate_af3(),
            step2: gpioa.pa8.into_alternate_af1(),
            err1: gpioc.pc5.into_pull_down_input(),
            err2: gpioc.pc4.into_pull_down_input(),
            battery_voltage: gpiob.pb1.into_analog(),
            error_led: gpiob.pb6.into_push_pull_output(),
            status_led: gpiob.pb7.into_push_pull_output(),
            can_rx: gpiob.pb8.into_alternate_af9(),
            can_tx: gpiob.pb9.into_alternate_af9(),
            scl: gpiob.pb10.into_alternate_af4_open_drain(),
            sda: gpiob.pb11.into_alternate_af4_open_drain(),
            usb_minus: gpioa.pa11.into_alternate_af10(),
            usb_plus: gpioa.pa12.into_alternate_af10(),
        }
    }
}

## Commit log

2020-12-16 Initial commit.
2020-12-16 Add thesis files.
2020-12-19 Start working on the schematic.
2020-12-25 Bring up the firmware project, try timer chaining for odometry reading.
2020-12-29 Add circuitry for the motor controllers.
2020-12-31 Add packages to components.
2021-01-04 Finish first version of the PCB, which is trash and shall perish.
2021-01-07 Implement more of the second version of the PCB.
2021-01-29 Finalize first HW version. Update firmware project.
2021-01-30 Refactor most of the firmware. Implement api for controller parts.
2021-01-30 Implement basic driver, start working on temperature and voltage monitoring.
2021-01-31 Finish temperature and voltage monitoring.
2021-02-01 Clean up the project.
2021-02-06 Add first ramp generator, add CI.
2021-02-07 Try to fix CI.
2021-02-07 Add HAL submodule using https.
2021-02-07 Revert: Add HAL submodule using https. Try to fix CI.
2021-02-07 Fix fmt, add information to debug docs.
2021-02-07 Fix fmt.
2021-02-07 Try to fix docs.
2021-02-07 Initial gh-pages commit
2021-02-07 Deploying to gh-pages from @ 752e19a94f0a64a7911354f5743c272d32707842 🚀
2021-02-07 Deploying to gh-pages from @ be6e15bdcb3bd198880e11482629d90770de29f3 🚀
2021-02-07 Try to improve docs CI performance.
2021-02-07 Deploying to gh-pages from @ 967dcaba7d86c007af7b2d5c70640edf73dff0f8 🚀
2021-02-09 Move code around a bit. Start working on CAN protocol implementation.
2021-02-17 Start improving the CANBus implementation.
2021-02-18 Add correct current setting.
2021-02-18 Deploying to gh-pages from @ dab7bfeadb4e194c8f12b87286e585194356948e 🚀
2021-02-21 Configure the thesis.
2021-02-25 Add failsafe timer, start implementing CANOpen.
2021-02-25 Deploying to gh-pages from @ eb375254c75be39589bc77e6666c258422be0436 🚀
2021-02-25 Add a section on requirements.
2021-02-25 Deploying to gh-pages from @ bbdad8495538d3a79d689d868a0134fa3e78589f 🚀
2021-02-28 Prepare second hardware revision.
2021-02-28 Deploying to gh-pages from @ a2c4435cee28c26c50e8210fe92e82e426ba4e09 🚀
2021-03-03 Start improving the second rev with feedback.
2021-03-03 Deploying to gh-pages from @ 3438889146f965db98ad7840118f2260d90385d4 🚀
2021-03-07 Make some final touches to the rev2 hardware.
2021-03-07 Deploying to gh-pages from @ 01ef76daeb7ba209d16ab6d78c827d8d8fb7d285 🚀
2021-03-08 Implement more of the encoder model. Make some final adjustments to rev2 board and order it.
2021-03-10 Improve encoder API, start writing tests for it.
2021-03-10 Deploying to gh-pages from @ 7032b9566fa9a96605fca2fadc6b99aa6672bd36 🚀
2021-03-11 Improve encoder API, start writing tests for it. #2
2021-03-11 Deploying to gh-pages from @ 3219f9f239eeef2da80fe49f862d6ac76c8ee74d 🚀
2021-03-11 Make final adjustments to the encoder abstraction.
2021-03-14 Refactor control using new abstraction.
2021-03-14 Start implementing simulated encoder, fix some warnings.
2021-03-14 Deploying to gh-pages from @ c529335b198bd66ffcb7787613b96296da9e0003 🚀
2021-03-15 Fix copypasta in Direction's opposite method.
2021-03-21 Change LED colors. Start working on object dictionary and specify PDO API.
2021-03-22 Move code around, start implementing driver that is independent on the hardware.
2021-03-22 Implement velocity control.
2021-03-23 UNTESTED: implement reception of PDOs and NMT commands. Fix some clippy problems and failing tests.
2021-03-23 Deploying to gh-pages from @ a15220b6b079181889f1b7b30d22df8249048d63 🚀
2021-03-24 Refactor.
2021-03-25 Deploying to gh-pages from @ 0ac2a098f6d8ce0231a0cfe483e0a8f6311430f6 🚀
2021-03-25 Deploying to gh-pages from @ b7c7411eb91283cc9e0b24c3d88df70da3776366 🚀
2021-03-28 Start working on the control application. Refactor shared. Refactor the thesis (split methods to multiple files).
2021-03-29 Start refactoring the sm4-controller.
2021-03-31 Write some of the introduction and related work.
2021-04-03 Write a section about KM3.
2021-04-03 Deploying to gh-pages from @ 6e43fdb93fe8fb3bdd732781455bf326cd10b740 🚀
2021-04-05 Finish related work.
2021-04-11 Add hardware design choices.
2021-04-15 Write about eeprom emulation.
2021-04-15 Add references from zotero.
2021-04-17 Write something about Rust.
2021-04-19 Write some more.
2021-04-19 Deploying to gh-pages from @ 39d091a4f714a2bbcf86d8220fd2d638b543d49a 🚀
2021-04-25 Add first TUI controller. Fix bugs in firmware found when testing the TUI controller.
2021-04-25 Deploying to gh-pages from @ 96f85a29d759874068b39e83e2a8b60f0e2da78f 🚀
2021-04-26 Start properly implementing NMT. Add untested current changing.
2021-04-26 Deploying to gh-pages from @ f3a93feb308f81a2139651451cdd3d98bd215b7b 🚀
2021-04-26 Add forgotten dependencies, make position_control work.
2021-04-26 Optimize speed changes. Start figuring out why
2021-04-26 Optimize speed changes. Tune position controller.
2021-04-27 Start refactoring positions, use upstream hal. Fix motion controller.
2021-04-27 Deploying to gh-pages from @ a347c7ed34871345616f296ea2f9cca1ce38b438 🚀
2021-04-27 Use const-generics for encoder resolution.
2021-04-27 Deploying to gh-pages from @ 1a0d818a71e6ba9b2d43bae579ecde1d72478af1 🚀
2021-04-27 Format code.
2021-04-27 Deploying to gh-pages from @ 17bcbdffacf830d4e41a2d578055e29782d67cf3 🚀
2021-04-27 Deploying to gh-pages from @ 154156a41e70035131b713235d23b314eb22c3e5 🚀
2021-04-27 Copy I2C from KM3. Remove some TODOs.
2021-04-27 Deploying to gh-pages from @ deaea9055cd6f7461615597ff96d0fcaf4ebaaea 🚀
2021-04-28 Use biber and biblatex.
2021-04-28 Deploying to gh-pages from @ 0891b2665d448d9474fc572e48394f8f89811803 🚀
2021-04-29 Add more text on Rust programming language.
2021-04-29 Deploying to gh-pages from @ 0e719408ea422a94f26a088431537f006d9dc3e1 🚀
2021-04-30 Add some text on steppers, update bibliography.
2021-04-30 Deploying to gh-pages from @ e8f4f6f8aee8db2dce7dd90b3ac34e620d1016aa 🚀
2021-04-30 Write some more text on stepper motors.
2021-04-30 Deploying to gh-pages from @ 4342771ef5328d9dcf12a5f72e32263fbeb51462 🚀
2021-05-01 Describe stepper control modes. Start working on driver ICs comparison.
2021-05-01 Deploying to gh-pages from @ 56d4a06a750b9480cbca1c3e8a931fc8a84971b4 🚀
2021-05-02 Update references.
2021-05-02 Deploying to gh-pages from @ 7ba3e9190d467c8b5378caf74f05a975a63bf12d 🚀
2021-05-02 Finish the section on steppers.
2021-05-03 Add some text on communication protocols.
2021-05-03 Deploying to gh-pages from @ a8f9351c0bd92c22e1003560d931eb7691b167ef 🚀
2021-05-03 Add some preliminary text on demonstration #1.
2021-05-03 Deploying to gh-pages from @ 4c11cc43890d7d4ddf775f2858bfb9b97103d99c 🚀
2021-05-03 Add some preliminary text on demonstration #2.
2021-05-03 Deploying to gh-pages from @ 4ee83a720651437cf1283744cac752b702f18267 🚀
2021-05-04 Describe parts of CANopen.
2021-05-04 Finish CANOpen for now.
2021-05-04 Deploying to gh-pages from @ 575486556e2fc55e600d4d8f91765e9238bc5713 🚀
2021-05-05 Finish the communication protocols section, update references.
2021-05-05 Add preliminary I2C support (buggy). Fix problem with blocking call on CANOpen.
2021-05-05 Deploying to gh-pages from @ 5c809a432993c344dbffba29f5acd3d9d4263392 🚀
2021-05-06 Deploying to gh-pages from @ 788b84b02f28377beaeff96ea5c5e10384a72090 🚀
2021-05-06 Refactor thesis structure.
2021-05-06 Update requirements.
2021-05-06 Start working on the embedded rust section.
2021-05-06 Deploying to gh-pages from @ 7d96a3779865d3c307666ee0862b62264355482b 🚀
2021-05-07 Describe embedded wg.
2021-05-07 Add text on register access and start working on the embedded-hal section.
2021-05-08 Add embedded-hal example.
2021-05-08 Add more text on embedded hal.
2021-05-09 Finish the sections on embedded rust.
2021-05-09 Start working on the text on electronics design.
2021-05-10 Describe most of the hardware.
2021-05-10 Finish the section on electronics design.
2021-05-10 Add some notes.
2021-05-10 Use new rust project directory structure, that promotes testing.
2021-05-10 Deploying to gh-pages from @ 055bc12528d73782125342aa360632c0ed394a1d 🚀
2021-05-10 Update actions recipes.
2021-05-11 Describe software stepper driver and monitoring.
2021-05-11 Deploying to gh-pages from @ 4ff5a6049736648539db4ae2ff01115f5bedc6c8 🚀
2021-05-11 Describe simulated encoders.
2021-05-11 Deploying to gh-pages from @ a1fe0f77b016648798adeb8f9d07374f4493903a 🚀
2021-05-11 [WIP] Traitify Object Dictionary to hide implementations.
2021-05-12 Add better API for object dictionary.
2021-05-12 Deploying to gh-pages from @ 812308f679d26212fece13f60b14b1e443cbfc82 🚀
2021-05-12 Implement more of the object dictionary functionality.
2021-05-12 Deploying to gh-pages from @ 59aa69cd5fb891b7bcf32890f52d428e3405784f 🚀
2021-05-12 Refactor object dictionary some more.
2021-05-12 Deploying to gh-pages from @ 3d37568a7179ef8ee9856c9d7c162cfce80473bd 🚀
2021-05-13 Document firmware architecture and control software.
2021-05-13 Deploying to gh-pages from @ b9ca9b18922966698b24411e0d55b101ecea8f28 🚀
2021-05-13 Document object dictionary.
2021-05-13 Describe CANOpen implementation.
2021-05-13 Fix problems in LaTeX.
2021-05-13 Deploying to gh-pages from @ 22a402afccc76ddc68cc48c1e6fb8a43e6ca11c3 🚀
2021-05-13 Deploying to gh-pages from @ 2b3728534437d5f72bea42c318b51e52bc006621 🚀
2021-05-14 Document I2C and CANOpen.
2021-05-14 Deploying to gh-pages from @ 5ff05422c3f1c14e23c76dfbab20ee2b4555cc9d 🚀
2021-05-14 Describe motion controller.
2021-05-15 Finish.
2021-05-15 Make software on par with the thesis.
2021-05-15 Deploying to gh-pages from @ 1c952e8e9b23a6d34db21e57ebb86ec4e2310fed 🚀
2021-05-15 Make some small code adjustments.
2021-05-15 Deploying to gh-pages from @ 869c43e60c7d93507631073e85c3cb7391908dac 🚀
2021-05-15 Add extended abstract.
2021-05-16 Finish, fix bugs.
2021-05-16 Deploying to gh-pages from @ f361192c723625a45669646605ca525dfd26e9b6 🚀
2021-05-17 Fix problem with image caption, add date to declaration.
2021-05-17 Deploying to gh-pages from @ 5df8906922532aef1c08b014b158fbc9f538ebaf 🚀
2021-05-17 Start working on the support for the second revision.
2021-05-17 Deploying to gh-pages from @ 7574446e372fb970241b998e958e7dba9ec8d2bd 🚀
2021-05-26 Add UI for position controller for demonstration.
2021-05-26 Start working on I2C backend.
2021-05-26 Deploying to gh-pages from @ d98671b96451dbfa6f0708f43668183aa481dd3d 🚀
2021-05-27 Add slideshow.
2021-05-27 Deploying to gh-pages from @ 51eede7808016d4eb0d3265d69d81d5882f531b2 🚀
2021-06-03 Add diacritics to the slideshow.
2021-06-03 Deploying to gh-pages from @ b65579c4c8e31828127cb0209892b61cbfbb8dca 🚀
2021-06-03 Fix some bugs, add more material to the slideshow.
2021-06-03 Deploying to gh-pages from @ 83d83b9a68da6f49d3256aea4af88a341ec5f599 🚀
2021-06-05 Improve the slideshow.
2021-06-05 Deploying to gh-pages from @ 2d3e10a54fed1a742fa40fde7213acdbd9cdf0e2 🚀

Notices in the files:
parts and their libraries:
Copyright 2016 Accelerated Designs. All rights reserved.
